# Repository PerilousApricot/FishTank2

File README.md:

# FishController
 PCBs and models for my reef-pi controller

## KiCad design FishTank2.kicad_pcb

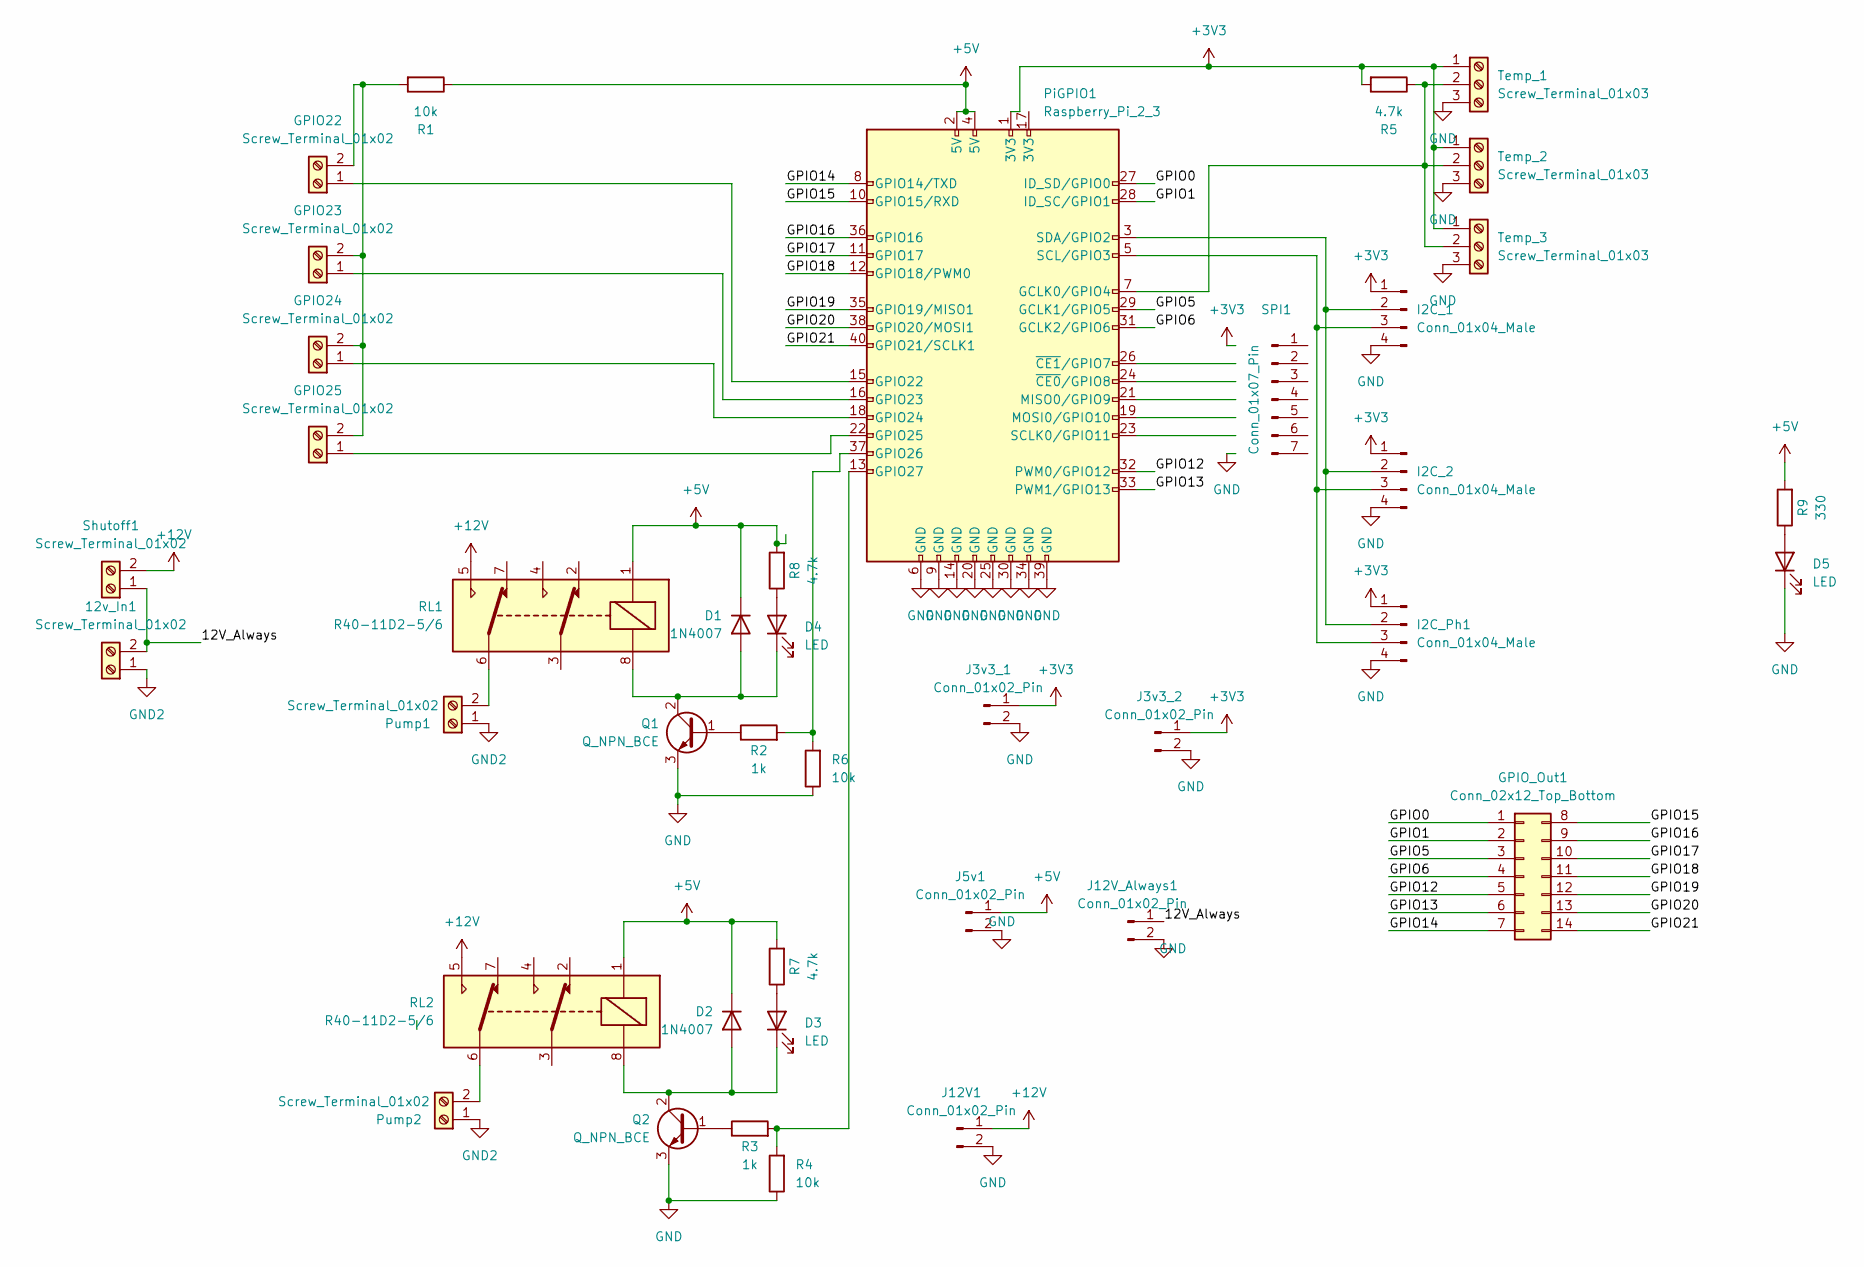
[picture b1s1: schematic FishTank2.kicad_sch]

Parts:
12v_In1: Screw_Terminal_01x02; TerminalBlock_Altech_AK300-2_P5.00mm
D1, D2: 1N4007; D_DO-41_SOD81_P7.62mm_Horizontal
D3, D4, D5: LED; LED_D1.8mm_W3.3mm_H2.4mm
GPIO22, GPIO23, GPIO24, GPIO25: Screw_Terminal_01x02; TerminalBlock_Altech_AK300-2_P5.00mm
GPIO_Out1: Conn_02x12_Top_Bottom; PinSocket_2x07_P2.54mm_Vertical
I2C_1, I2C_2, I2C_Ph1: Conn_01x04_Male; PinHeader_1x04_P2.54mm_Vertical
J3v3_1, J3v3_2, J5v1, J12V1, J12V_Always1: Conn_01x02_Pin; PinHeader_1x02_P2.54mm_Vertical
PiGPIO1: Raspberry_Pi_2_3; PinHeader_2x20_P2.54mm_Vertical
Pump1, Pump2: Screw_Terminal_01x02; TerminalBlock_Altech_AK300-2_P5.00mm
Q1, Q2: Q_NPN_BCE; TO-92
R1, R4, R6: 10k; R_Axial_DIN0204_L3.6mm_D1.6mm_P5.08mm_Horizontal
R2, R3: 1k; R_Axial_DIN0204_L3.6mm_D1.6mm_P5.08mm_Horizontal
R5, R7, R8: 4.7k; R_Axial_DIN0204_L3.6mm_D1.6mm_P5.08mm_Horizontal
R9: 330; R_Axial_DIN0204_L3.6mm_D1.6mm_P5.08mm_Horizontal
RL1, RL2: R40-11D2-5/6; Relay_DPDT_NTE_NRP04
SPI1: Conn_01x07_Pin; PinHeader_1x07_P2.54mm_Vertical
Shutoff1: Screw_Terminal_01x02; TerminalBlock_Altech_AK300-2_P5.00mm
Temp_1, Temp_2, Temp_3: Screw_Terminal_01x03; TerminalBlock_Altech_AK300-3_P5.00mm

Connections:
+3V3: I2C_1.1, I2C_2.1, I2C_Ph1.1, J3v3_1.1, J3v3_2.1, PiGPIO1.1 (3V3), R5.2, Temp_1.1, Temp_2.1, Temp_3.1
+5V: D1.1 (K), D2.1 (K), J5v1.1, PiGPIO1.2 (5V), PiGPIO1.4 (5V), R1.1, R7.2, R8.2, R9.2, RL1.1, RL2.1
+12V: J12V1.1, RL1.5, RL2.5, Shutoff1.2
/12V_Always: 12v_In1.2, J12V_Always1.1, Shutoff1.1
/GPIO0: GPIO_Out1.1, PiGPIO1.27 (ID_SD/GPIO0)
/GPIO1: GPIO_Out1.2, PiGPIO1.28 (ID_SC/GPIO1)
/GPIO5: GPIO_Out1.3, PiGPIO1.29 (GCLK1/GPIO5)
/GPIO6: GPIO_Out1.4, PiGPIO1.31 (GCLK2/GPIO6)
/GPIO12: GPIO_Out1.5, PiGPIO1.32 (PWM0/GPIO12)
/GPIO13: GPIO_Out1.6, PiGPIO1.33 (PWM1/GPIO13)
/GPIO14: GPIO_Out1.7, PiGPIO1.8 (GPIO14/TXD)
/GPIO15: GPIO_Out1.8, PiGPIO1.10 (GPIO15/RXD)
/GPIO16: GPIO_Out1.9, PiGPIO1.36 (GPIO16)
/GPIO17: GPIO_Out1.10, PiGPIO1.11 (GPIO17)
/GPIO18: GPIO_Out1.11, PiGPIO1.12 (GPIO18/PWM0)
/GPIO19: GPIO_Out1.12, PiGPIO1.35 (GPIO19/MISO1)
/GPIO20: GPIO_Out1.13, PiGPIO1.38 (GPIO20/MOSI1)
/GPIO21: GPIO_Out1.14, PiGPIO1.40 (GPIO21/SCLK1)
GND: D5.1 (K), I2C_1.4, I2C_2.4, I2C_Ph1.4, J3v3_1.2, J3v3_2.2, J5v1.2, J12V1.2, J12V_Always1.2, PiGPIO1.6 (GND), PiGPIO1.9 (GND), PiGPIO1.14 (GND), PiGPIO1.20 (GND), PiGPIO1.25 (GND), PiGPIO1.30 (GND), PiGPIO1.34 (GND), PiGPIO1.39 (GND), Q1.3 (E), Q2.3 (E), R4.1, R6.1, Temp_1.3, Temp_2.3, Temp_3.3
GND2: 12v_In1.1, Pump1.1, Pump2.1
unnamed: D1.2 (A), D4.1 (K), Q1.2 (C), RL1.8
unnamed: D2.2 (A), D3.1 (K), Q2.2 (C), RL2.8
unnamed: D3.2 (A), R7.1
unnamed: D4.2 (A), R8.1
unnamed: D5.2 (A), R9.1
unnamed: GPIO22.1, PiGPIO1.15 (GPIO22)
unnamed: GPIO22.2, GPIO23.2, GPIO24.2, GPIO25.2, R1.2
unnamed: GPIO23.1, PiGPIO1.16 (GPIO23)
unnamed: GPIO24.1, PiGPIO1.18 (GPIO24)
unnamed: GPIO25.1, PiGPIO1.22 (GPIO25)
unnamed: I2C_1.2, I2C_2.2, I2C_Ph1.2, PiGPIO1.3 (SDA/GPIO2)
unnamed: I2C_1.3, I2C_2.3, I2C_Ph1.3, PiGPIO1.5 (SCL/GPIO3)
unnamed: PiGPIO1.7 (GCLK0/GPIO4), R5.1, Temp_1.2, Temp_2.2, Temp_3.2
unnamed: PiGPIO1.37 (GPIO26), R2.2, R6.2
unnamed: PiGPIO1.13 (GPIO27), R3.2, R4.2
unnamed: Pump1.2, RL1.6
unnamed: Pump2.2, RL2.6
unnamed: Q1.1 (B), R2.1
unnamed: Q2.1 (B), R3.1

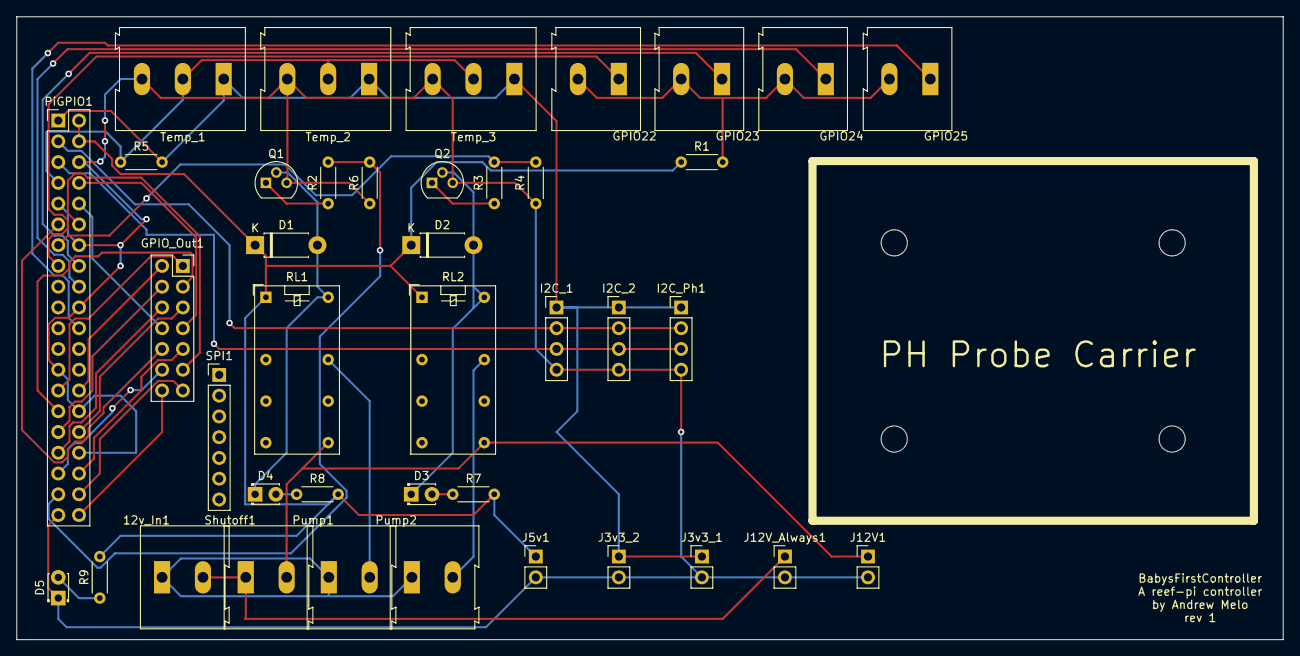
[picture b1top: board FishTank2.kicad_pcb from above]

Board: 2 copper layers, 154.9 x 76.2 mm, 40 parts (0 on the bottom side), 39 nets.

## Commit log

2023-07-03 Update .gitignore
    Dont store .gbr files
2023-07-03 Move trace away from Ph sensor
